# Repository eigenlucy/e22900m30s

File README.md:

# e22900m30s LoRa transciever

CDBYTE E22-900M30S 30dBm (22dBm+8dBm PA) LoRa transciever. Based on the SX1262 LoRa IC.

[See this repo for a detailed overview of the module with schematics and 3D models](https://github.com/S5NC/CDEBYTE_Modules)

[See my hackaday post on the E22-900M30S for a graph of TX power vs Vin](https://hackaday.io/project/202604-femtofox-pro-tx-power-power-consumption-testing)

Created by lucy moglia <eigenlucy@proton.me>

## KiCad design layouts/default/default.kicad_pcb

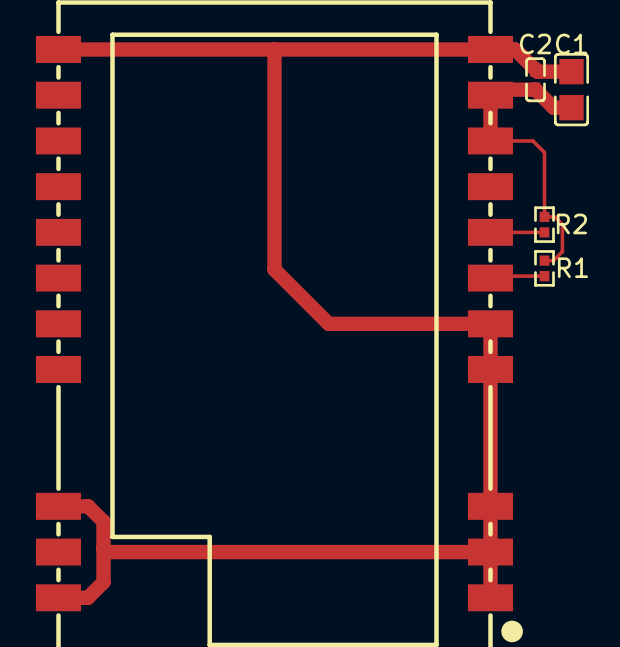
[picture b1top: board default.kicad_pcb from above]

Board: 2 copper layers, 5 parts (0 on the bottom side), 4 nets.

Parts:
C1: 10µF ±10% 25V X5R; C0805-3b2e55
C2: 100nF ±10% 16V X7R; C0402-b3ef17
R1, R2: 10kΩ ±1% 62.5mW; R0402-56259e
U1: WIRELM-SMD_E22-900M30S-98c301

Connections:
RXEN: R1.2, U1.6
TXEN: R2.2, U1.7
gnd: C1.2, C2.2, U1.1, U1.2, U1.3, U1.4, U1.5, U1.11, U1.12, U1.20, U1.22
hv: C1.1, C2.1, R1.1, R2.1, U1.9, U1.10

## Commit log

2025-04-24 v01.1.0
2025-04-25 fixed yaml
2025-04-25 readme
2025-04-30 changed app name
